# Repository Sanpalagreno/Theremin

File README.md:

# Theremin

This second image is the work I have completed after my second session. I had to learn how to make new symbols because the part I want to use doesnt have a built in one.

This is the schematic so far, it is almost done. I learned how to make my own symbols for the parts KiCAD didnt have. It is going very well but I have a lot of work ahead. 2026-10-23

I finished the schematic, it is by far the larges ont I have made. 2026-10-24

I finished the PCB for the theremin.

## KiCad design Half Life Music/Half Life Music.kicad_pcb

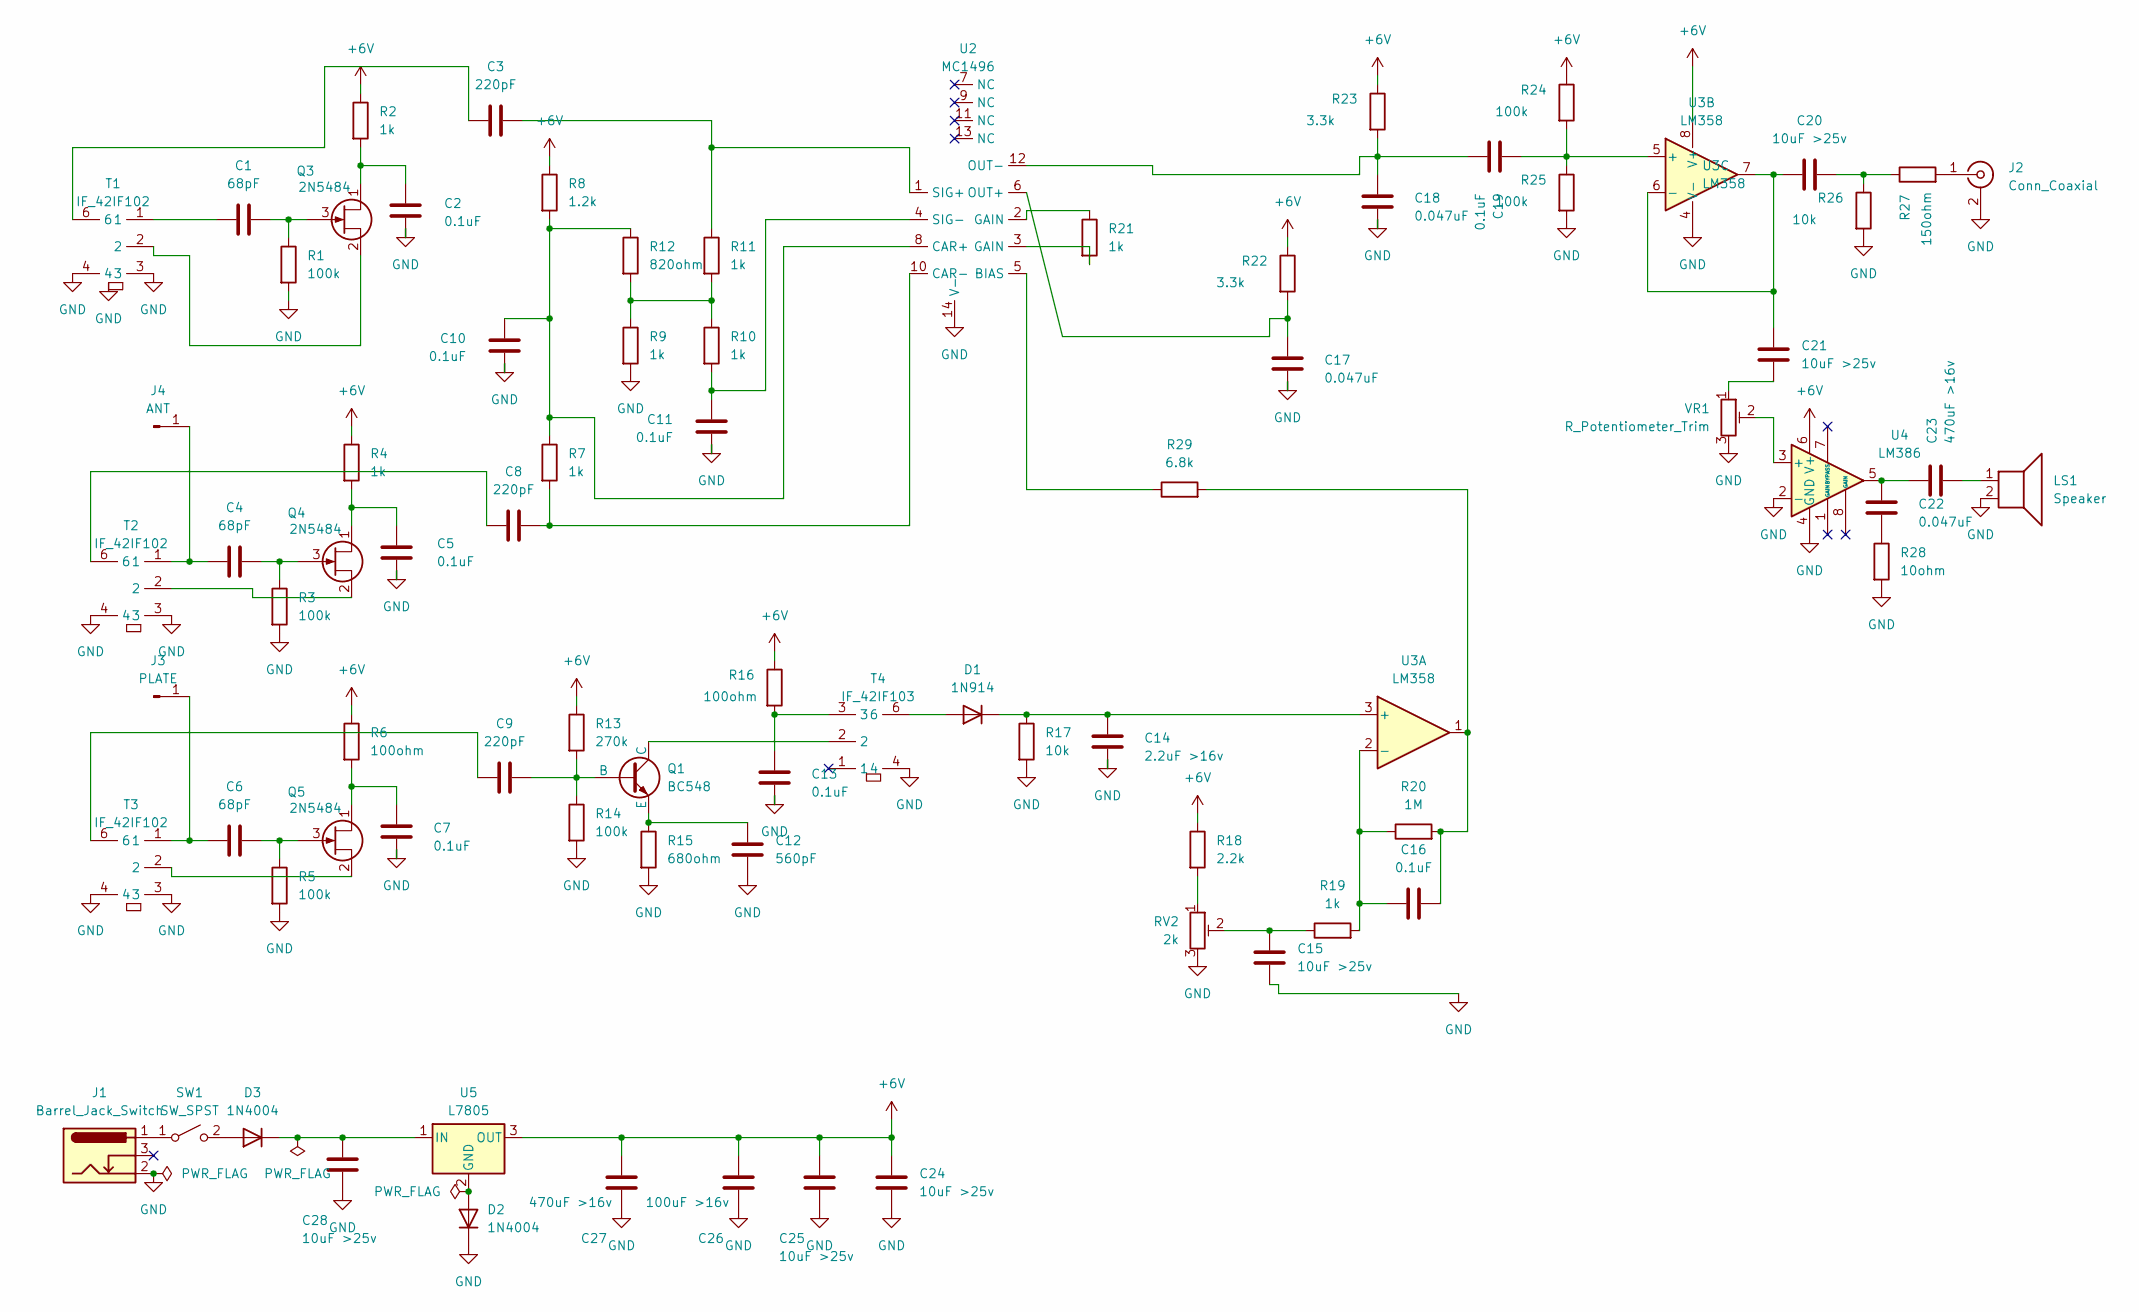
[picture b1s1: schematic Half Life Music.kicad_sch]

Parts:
C1, C4, C6: 68pF; C_Disc_D5.0mm_W2.5mm_P5.00mm
C2, C5, C7, C10, C11, C13, C16, C19: 0.1uF; C_Disc_D5.0mm_W2.5mm_P5.00mm
C3, C8, C9: 220pF; C_Disc_D5.0mm_W2.5mm_P5.00mm
C12: 560pF; C_Disc_D5.0mm_W2.5mm_P5.00mm
C14: 2.2uF >16v; CP_Radial_D5.0mm_P2.00mm
C15, C20, C21, C24, C25, C28: 10uF >25v; CP_Radial_D5.0mm_P2.00mm
C17, C18, C22: 0.047uF; C_Disc_D5.0mm_W2.5mm_P5.00mm
C23: 470uF >16v; SOIC-8_3.9x4.9mm_P1.27mm
C26: 100uF >16v; CP_Radial_D6.3mm_P2.50mm
C27: 470uF >16v; CP_Radial_D8.0mm_P3.50mm
D1: 1N914; D_DO-35_SOD27_P7.62mm_Horizontal
D2, D3: 1N4004; D_DO-41_SOD81_P10.16mm_Horizontal
J1: Barrel_Jack_Switch; FanPinHeader_1x03_P2.54mm_Vertical
J2: Conn_Coaxial; PinHeader_1x02_P2.54mm_Vertical
J3: PLATE; PinHeader_1x01_P1.00mm_Horizontal
J4: ANT; PinHeader_1x01_P1.00mm_Horizontal
LS1: Speaker; PinHeader_1x02_P2.54mm_Vertical
Q1: BC548; TO-92_Inline
Q3, Q4, Q5: 2N5484; TO-92_Inline
R1, R3, R5, R14, R24, R25: 100k; R_Axial_DIN0207_L6.3mm_D2.5mm_P10.16mm_Horizontal
R2, R4, R7, R9, R10, R11, R19, R21: 1k; R_Axial_DIN0207_L6.3mm_D2.5mm_P10.16mm_Horizontal
R6, R16: 100ohm; R_Axial_DIN0207_L6.3mm_D2.5mm_P10.16mm_Horizontal
R8: 1.2k; R_Axial_DIN0207_L6.3mm_D2.5mm_P10.16mm_Horizontal
R12: 820ohm; R_Axial_DIN0207_L6.3mm_D2.5mm_P10.16mm_Horizontal
R13: 270k; R_Axial_DIN0207_L6.3mm_D2.5mm_P10.16mm_Horizontal
R15: 680ohm; R_Axial_DIN0207_L6.3mm_D2.5mm_P10.16mm_Horizontal
R17, R26: 10k; R_Axial_DIN0207_L6.3mm_D2.5mm_P10.16mm_Horizontal
R18: 2.2k; R_Axial_DIN0207_L6.3mm_D2.5mm_P10.16mm_Horizontal
R20: 1M; R_Axial_DIN0207_L6.3mm_D2.5mm_P10.16mm_Horizontal
R22, R23: 3.3k; R_Axial_DIN0207_L6.3mm_D2.5mm_P10.16mm_Horizontal
R27: 150ohm; R_Axial_DIN0207_L6.3mm_D2.5mm_P10.16mm_Horizontal
R28: 10ohm; R_Axial_DIN0207_L6.3mm_D2.5mm_P10.16mm_Horizontal
R29: 6.8k; R_Axial_DIN0207_L6.3mm_D2.5mm_P10.16mm_Horizontal
RV2: 2k; Potentiometer_Bourns_3386P_Vertical
SW1: SW_SPST; PinHeader_1x02_P2.54mm_Vertical
T1, T2, T3: IF_42IF102; IF_42IF_10E
T4: IF_42IF103; IF_42IF_10E
U2: MC1496; DIP-14_W7.62mm
U3: LM358; DIP-8_W7.62mm
U4: LM386; DIP-8_W7.62mm
U5: L7805; TO-220-3_Vertical
VR1: R_Potentiometer_Trim; FanPinHeader_1x03_P2.54mm_Vertical

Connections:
+6V: C24.2, C25.2, C26.2, C27.2, R2.1, R4.1, R6.1, R8.1, R13.1, R16.1, R18.1, R22.1, R23.1, R24.1, U3.8 (V+), U4.6 (V+), U5.3 (OUT)
GND: C2.2, C5.2, C7.2, C10.2, C11.2, C12.1, C13.2, C14.2, C15.2, C17.2, C18.2, C24.1, C25.1, C26.1, C27.1, C28.1, D2.1 (K), J1.2, J2.2 (Ext), LS1.2, R1.2, R3.2, R5.2, R9.2, R14.2, R15.2, R17.2, R25.2, R26.2, R28.2, RV2.3, T1.3, T1.4, T2.3, T2.4, T3.3, T3.4, T4.4, U2.14 (V-), U3.4 (V-), U4.2 (-), U4.4 (GND), VR1.3
unnamed: C1.1, T1.1
unnamed: C1.2, Q3.3 (G), R1.1
unnamed: C2.1, Q3.1 (D), R2.2
unnamed: C3.1, T1.6
unnamed: C4.2, Q4.3 (G), R3.1
unnamed: C5.1, Q4.1 (D), R4.2
unnamed: C6.2, Q5.3 (G), R5.1
unnamed: C7.1, Q5.1 (D), R6.2
unnamed: C8.1, T2.6
unnamed: C9.1, T3.6
unnamed: C13.1, R16.2, T4.3
unnamed: C15.1, R19.1, RV2.2
unnamed: C16.2, R20.2, R29.2, U3.1
unnamed: C20.2, R26.1, R27.1
unnamed: C21.2, VR1.1
unnamed: C22.1, C23.1, U4.5
unnamed: C22.2, R28.1
unnamed: C23.2, LS1.1
unnamed: D1.2 (A), T4.6
unnamed: C14.1, D1.1 (K), R17.1, U3.3 (+)
unnamed: D2.2 (A), U5.2 (GND)
unnamed: D3.2 (A), SW1.2 (B)
unnamed: C28.2, D3.1 (K), U5.1 (IN)
unnamed: J2.1 (In), R27.2
unnamed: C6.1, J3.1 (Pin_1_1), T3.1
unnamed: C4.1, J4.1 (Pin_1_1), T2.1
unnamed: C9.2, Q1.2 (B), R13.2, R14.1
unnamed: Q1.1 (C), T4.2
unnamed: C12.2, Q1.3 (E), R15.1
unnamed: Q3.2 (S), T1.2
unnamed: Q4.2 (S), T2.2
unnamed: Q5.2 (S), T3.2
unnamed: R9.1, R10.1, R11.2, R12.2
unnamed: R18.2, RV2.1
unnamed: R21.1, U2.2 (GAIN)
unnamed: R21.2, U2.3 (GAIN)
unnamed: J1.1, SW1.1 (A)
unnamed: R29.1, U2.5 (BIAS)
unnamed: C10.1, R7.1, R8.2, R12.1, U2.8 (CAR+)
unnamed: C8.2, R7.2, U2.10 (CAR-)
unnamed: C17.1, R22.2, U2.6 (OUT+)
unnamed: C18.1, C19.2, R23.2, U2.12 (OUT-)
unnamed: C3.2, R11.1, U2.1 (SIG+)
unnamed: C11.1, R10.2, U2.4 (SIG-)
unnamed: C16.1, R19.2, R20.1, U3.2 (-)
unnamed: C19.1, R24.2, R25.1, U3.5 (+)
unnamed: C20.1, C21.1, U3.6 (-), U3.7
unnamed: U4.3 (+), VR1.2

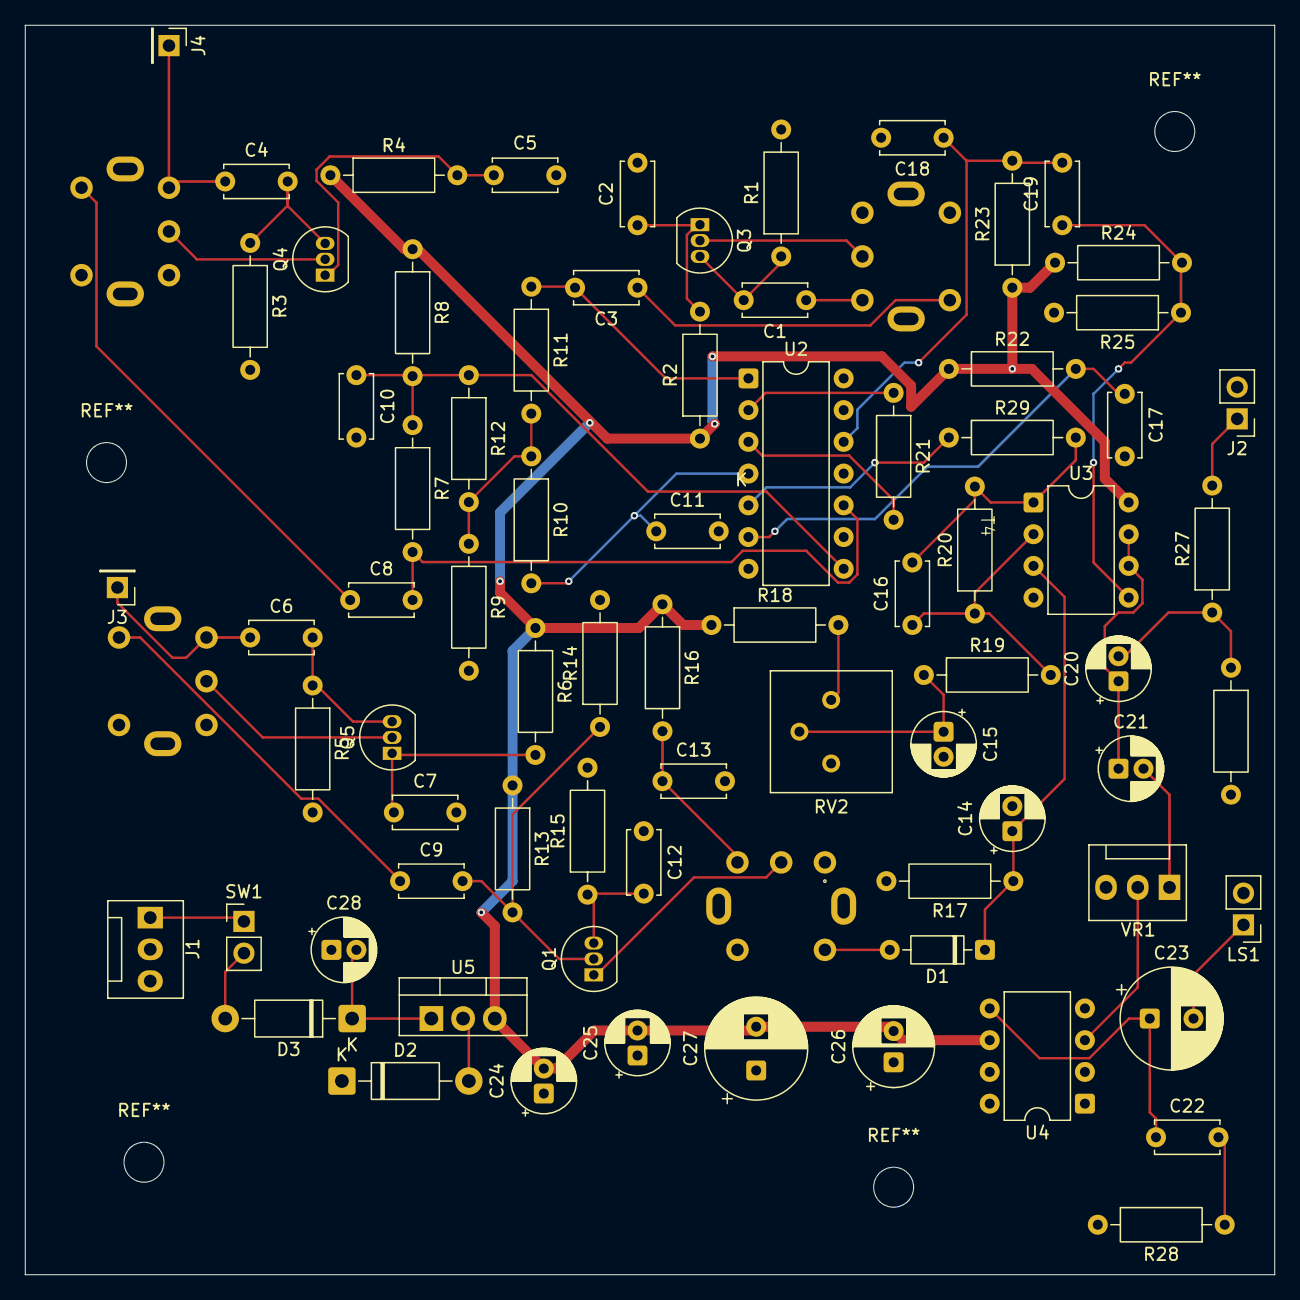
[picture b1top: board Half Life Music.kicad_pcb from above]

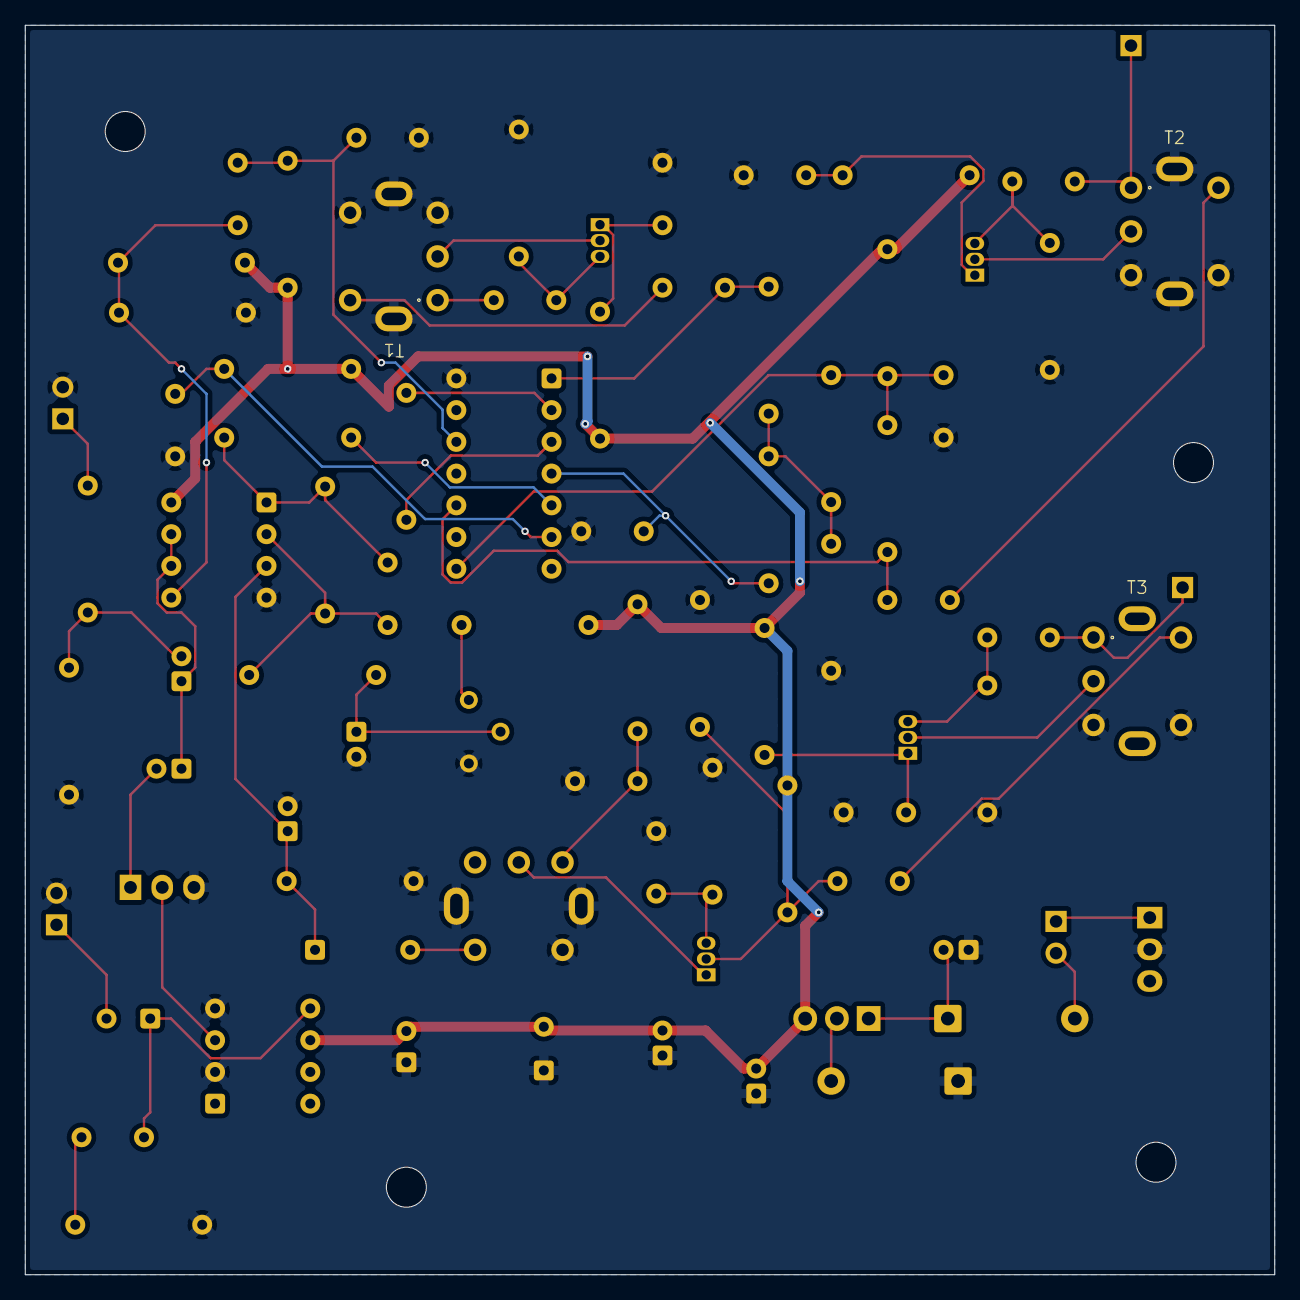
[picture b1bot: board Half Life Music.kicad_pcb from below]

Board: 2 copper layers, 100.0 x 100.0 mm, 80 parts (3 on the bottom side), 50 nets.
